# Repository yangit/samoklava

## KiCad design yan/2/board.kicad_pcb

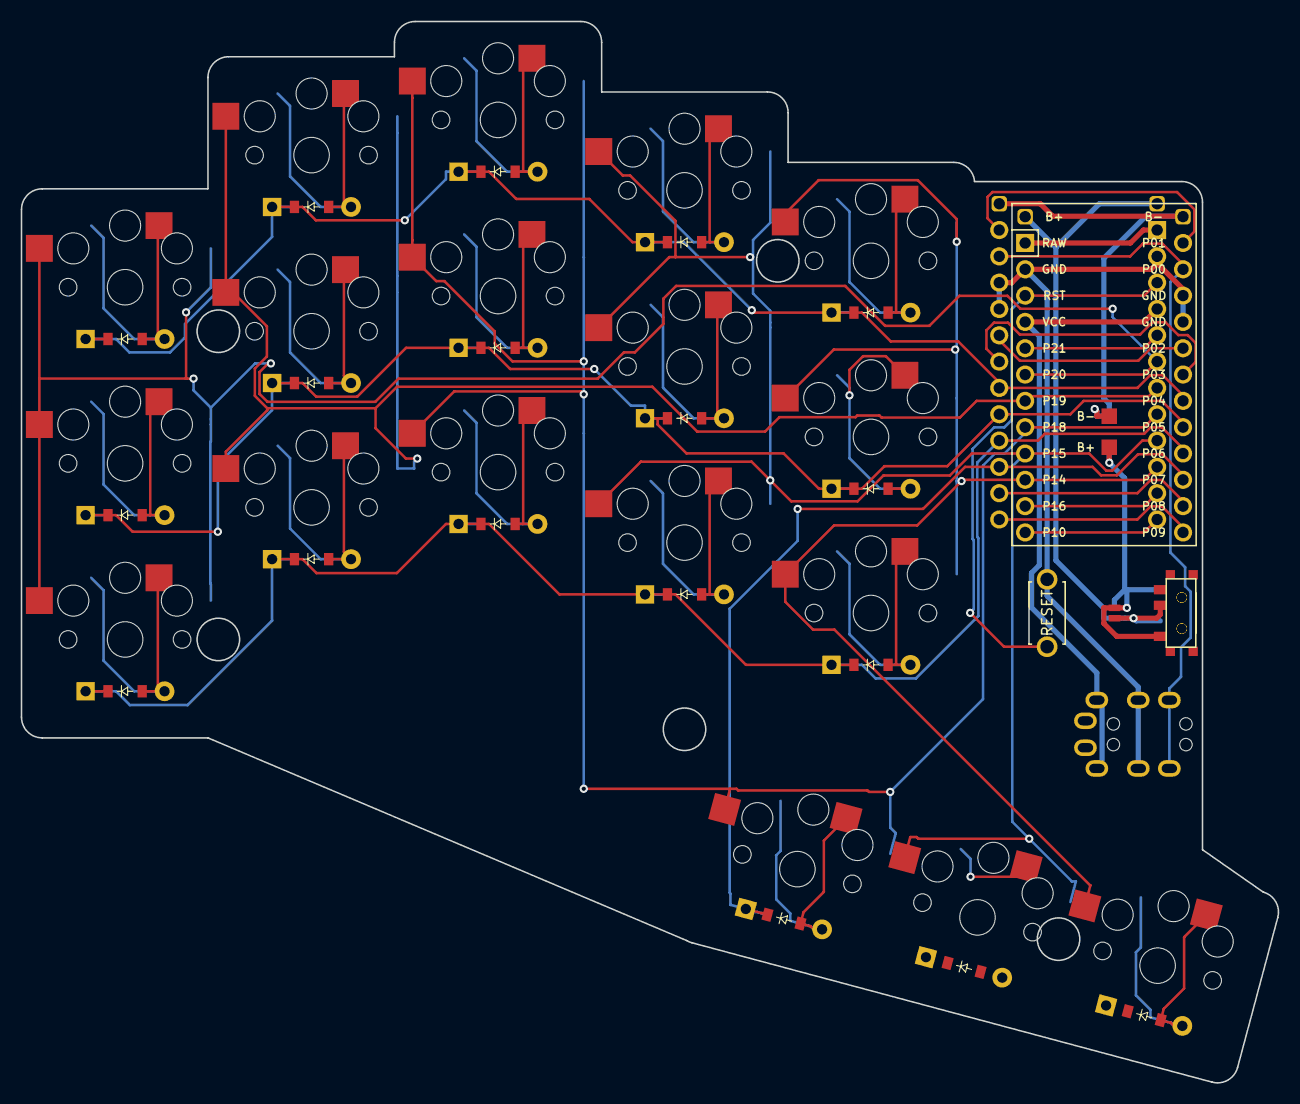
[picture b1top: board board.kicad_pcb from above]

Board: 2 copper layers, 121.3 x 102.5 mm, 47 parts (0 on the bottom side), 43 nets.

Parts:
B1: ResetSW
D1, D2, D3, D4, D5, D6, D7, D8, D9, D10, D11, D12, D13, D14, D15, D16, D17, D18: ComboDiode
J1, J2: Jumper
MCU1, MCU2: ProMicro
PAD1, PAD2: SMDPad
S1, S2, S3, S4, S5, S6, S7, S8, S9, S10, S11, S12, S13, S14, S15, S16, S17, S18: PG1350
T1, T2: SPDT_C128955
TRRS1, TRRS2: TRRS-PJ-320A-dual

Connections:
Bminus: MCU1.25, MCU2.25, PAD2.1
Bplus: J1.2, J2.2, MCU1.25, MCU2.25, T1.2, T2.2
Braw: J1.1, J2.1, PAD1.1, T1.1, T2.1
GND: B1.2, MCU1.2, MCU1.15, MCU1.16, MCU2.2, MCU2.15, MCU2.16, TRRS1.3, TRRS2.3
P0: MCU1.14, MCU2.14, TRRS1.4, TRRS2.4
P1: MCU1.13, MCU2.13
P2: MCU1.17, MCU2.17
P3: MCU1.18, MCU2.18
P4: D3.1, D3.2, D6.1, D6.2, D9.1, D9.2, D12.1, D12.2, D15.1, D15.2, MCU1.19, MCU2.19
P5: D2.1, D2.2, D5.1, D5.2, D8.1, D8.2, D11.1, D11.2, D14.1, D14.2, MCU1.20, MCU2.20
P6: D1.1, D1.2, D4.1, D4.2, D7.1, D7.2, D10.1, D10.2, D13.1, D13.2, MCU1.21, MCU2.21
P7: D16.1, D16.2, D17.1, D17.2, D18.1, D18.2, MCU1.22, MCU2.22
P8: MCU1.23, MCU2.23
P9: MCU1.24, MCU2.24
P10: MCU1.12, MCU2.12
P14: MCU1.10, MCU2.10, S13.2, S14.2, S15.2, S18.2
P15: MCU1.9, MCU2.9, S10.2, S11.2, S12.2, S17.2
P16: MCU1.11, MCU2.11
P18: MCU1.8, MCU2.8, S7.2, S8.2, S9.2, S16.2
P19: MCU1.7, MCU2.7, S4.2, S5.2, S6.2
P20: MCU1.6, MCU2.6, S1.2, S2.2, S3.2
P21: MCU1.5, MCU2.5
RAW: MCU1.1, MCU2.1
RST: B1.1, MCU1.3, MCU2.3
VCC: MCU1.4, MCU2.4, TRRS1.2, TRRS2.2
far_thumb: D18.1, D18.2, S18.1
home_thumb: D17.1, D17.2, S17.1
index_bottom: D10.1, D10.2, S10.1
index_home: D11.1, D11.2, S11.1
index_top: D12.1, D12.2, S12.1
inner_bottom: D13.1, D13.2, S13.1
inner_home: D14.1, D14.2, S14.1
inner_top: D15.1, D15.2, S15.1
middle_bottom: D7.1, D7.2, S7.1
middle_home: D8.1, D8.2, S8.1
middle_top: D9.1, D9.2, S9.1
near_thumb: D16.1, D16.2, S16.1
pinky_bottom: D1.1, D1.2, S1.1
pinky_home: D2.1, D2.2, S2.1
pinky_top: D3.1, D3.2, S3.1
ring_bottom: D4.1, D4.2, S4.1
ring_home: D5.1, D5.2, S5.1
ring_top: D6.1, D6.2, S6.1

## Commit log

2022-04-19 Yan layout v2
2022-04-19 re push
2022-04-19 Add v2
2022-04-20 v3, no trrs, move holes, remve lable
2022-04-21 trrs back
